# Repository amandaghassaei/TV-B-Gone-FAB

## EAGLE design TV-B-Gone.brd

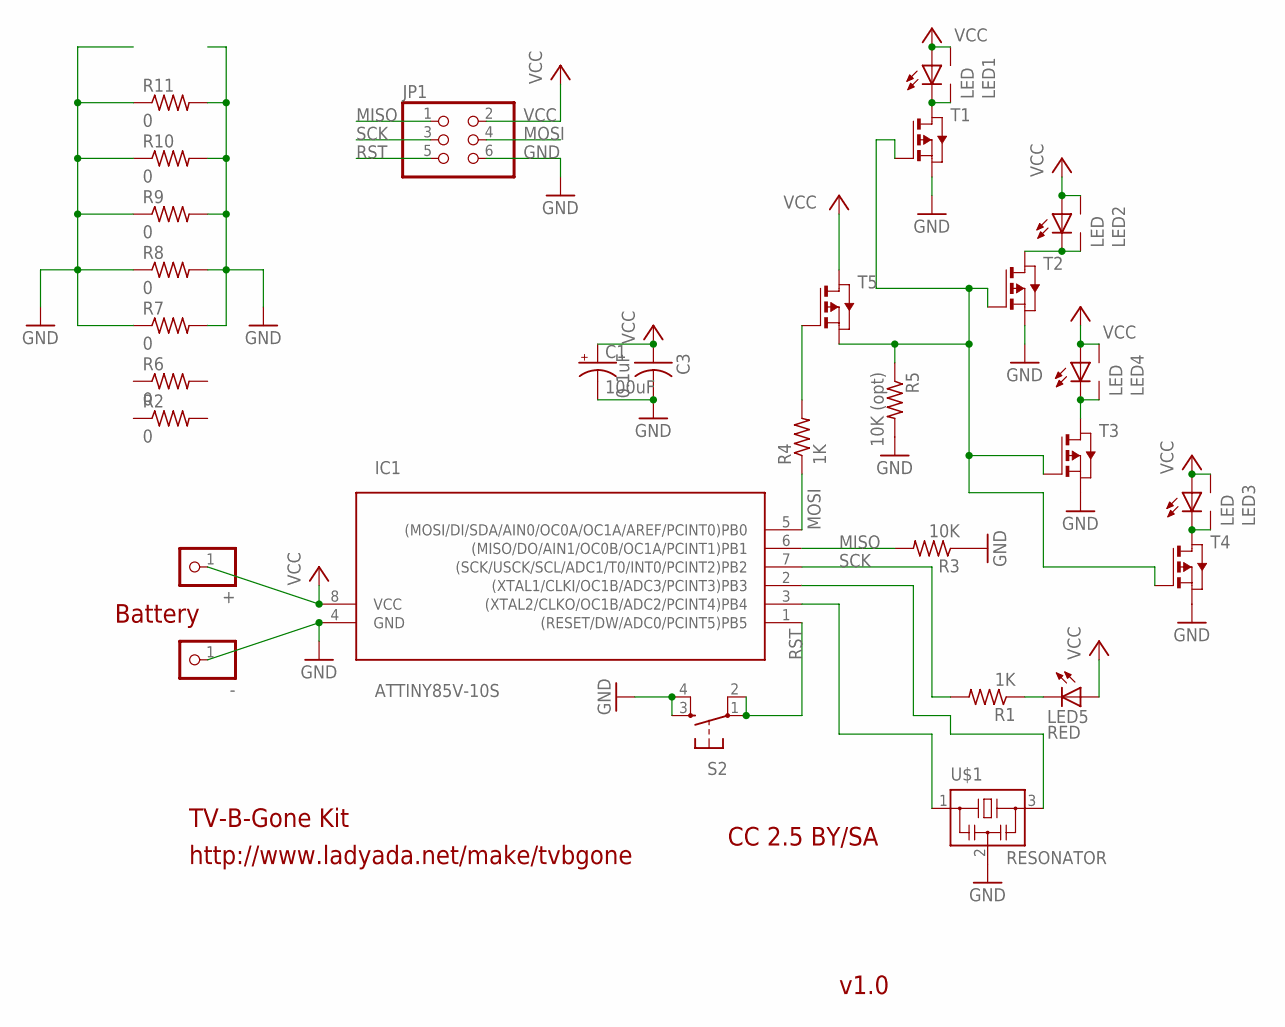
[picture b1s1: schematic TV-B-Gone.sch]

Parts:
+: PINHD-1X1; 1X01
-: PINHD-1X1; 1X01
C1: 100uF; PANASONIC_E
C3: 0.1uF; C1206FAB
IC1: ATTINY85V-10S; SOIC8
JP1: PINHD-2X3-SMD; 2X03SMD
LED1, LED2, LED3, LED4: LED; 5MM-SIDE
LED5: RED; CHIPLED_1206
R1, R4: 1K; R1206FAB
R2, R6, R7, R8, R9, R10, R11: 0; R1206FAB
R3: 10K; R1206FAB
R5: 10K (opt); R1206FAB
S2: 6MM_SWITCH6MM_SWITCH; 6MM_SWITCH
T1, T2, T3, T4, T5: PMOSFETSOT23; SOT-23
U$1: RESONATOR; EFOBM

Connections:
GND: -.1, C1.-, C3.2, IC1.4 (GND), JP1.6, R3.1, R5.2, R7.1, R7.2, R8.1, R8.2, R9.1, R9.2, R10.1, R10.2, R11.1, R11.2, S2.3 (S), S2.4 (S1), T1.2 (S), T2.2 (S), T3.2 (S), T4.2 (S), U$1.2
MISO: IC1.6 ((MISO/DO/AIN1/OC0B/OC1A/PCINT1)PB1), JP1.1, R3.2
MOSI: IC1.5 ((MOSI/DI/SDA/AIN0/OC0A/OC1A/AREF/PCINT0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), JP1.4, R4.1
unnamed: IC1.3 ((XTAL2/CLKO/OC1B/ADC2/PCINT4)PB4), U$1.1
unnamed: IC1.2 ((XTAL1/CLKI/OC1B/ADC3/PCINT3)PB3), U$1.3
unnamed: LED5.C, R1.1
unnamed: R4.2, T5.3 (G)
unnamed: LED4.K (C), LED4.K2 (C1), T3.1 (D)
unnamed: LED2.K (C), LED2.K2 (C1), T2.1 (D)
unnamed: LED3.K (C), LED3.K2 (C1), T4.1 (D)
unnamed: R5.1, T1.3 (G), T2.3 (G), T3.3 (G), T4.3 (G), T5.2 (S)
unnamed: LED1.K (C), LED1.K2 (C1), T1.1 (D)
RST: IC1.1 ((RESET/DW/ADC0/PCINT5)PB5), JP1.5, S2.1, S2.2 (P1)
SCK: IC1.7 ((SCK/USCK/SCL/ADC1/T0/INT0/PCINT2)PB2), JP1.3, R1.2
VCC: +.1, C1.+, C3.1, IC1.8 (VCC), JP1.2, LED1.A, LED1.A2 (A1), LED2.A, LED2.A2 (A1), LED3.A, LED3.A2 (A1), LED4.A, LED4.A2 (A1), LED5.A, T5.1 (D)

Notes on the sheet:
http://www.ladyada.net/make/tvbgone
TV-B-Gone Kit
v1.0
CC 2.5 BY/SA
Battery

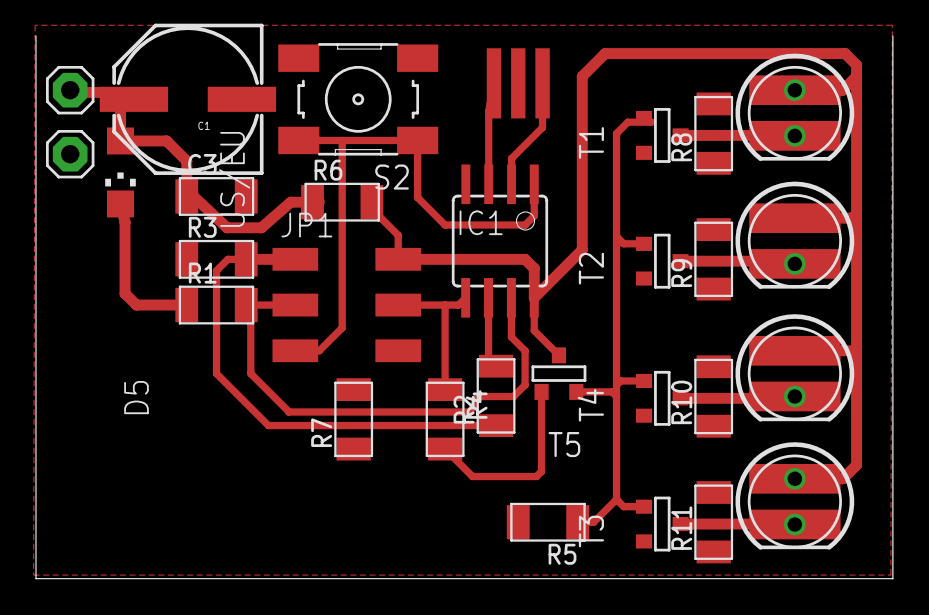
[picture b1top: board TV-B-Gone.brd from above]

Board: 2 copper layers, 47.6 x 30.1 mm, 29 parts (0 on the bottom side), 15 nets.

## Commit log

2016-05-26 small changes
2016-05-28 smd cap
2016-05-28 rename
2016-05-28 separating traces

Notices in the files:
parts and their libraries:
SparkFun-Capacitors: Licensing: Creative Commons ShareAlike 4.0 International - https://creativecommons.org/licenses/by-sa/4.0
